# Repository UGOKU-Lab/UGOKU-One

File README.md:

UGOKU One のハードウェア（KiCad）リポジトリです。

[UGOKU One WEBサイト](https://ugoku-lab.github.io/ugokuone.html)

UGOKU One はモータやセンサを使ったロボットなどのDIY製作物を少しでも手軽に操作することを目的に開発しているオープンソースハードウェアの汎用基板です。
    
- 単四電池ボックス搭載で単四電池4本でDCモーターやRCサーボをの駆動が可能
- Arduinoで開発可能なESP32マイコン搭載(無線通信対応)
- DCモータドライバ（TB67H450FNG）を2個搭載
- 豊富な汎用IOポートでいろんな拡張が可能
- 圧着工具を使用せずにモーターやセンサーの配線が可能

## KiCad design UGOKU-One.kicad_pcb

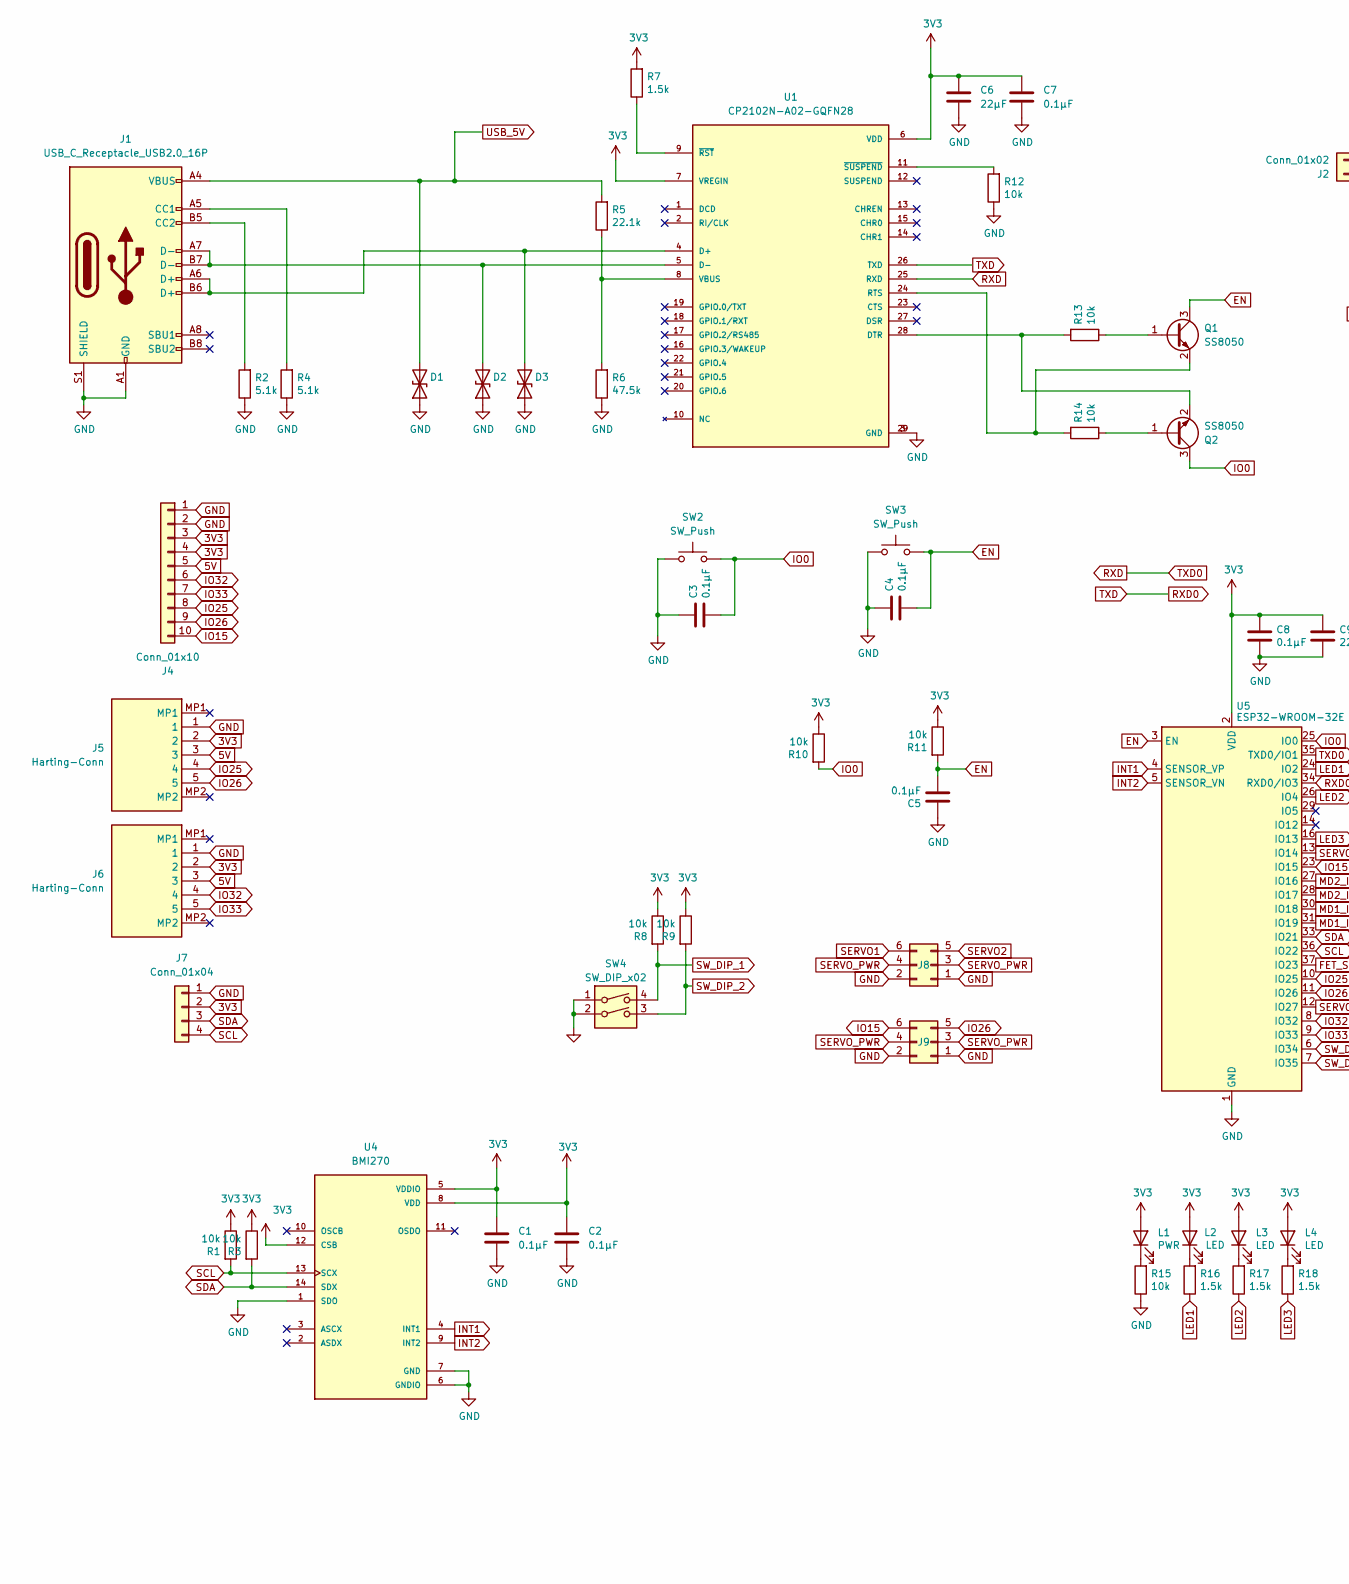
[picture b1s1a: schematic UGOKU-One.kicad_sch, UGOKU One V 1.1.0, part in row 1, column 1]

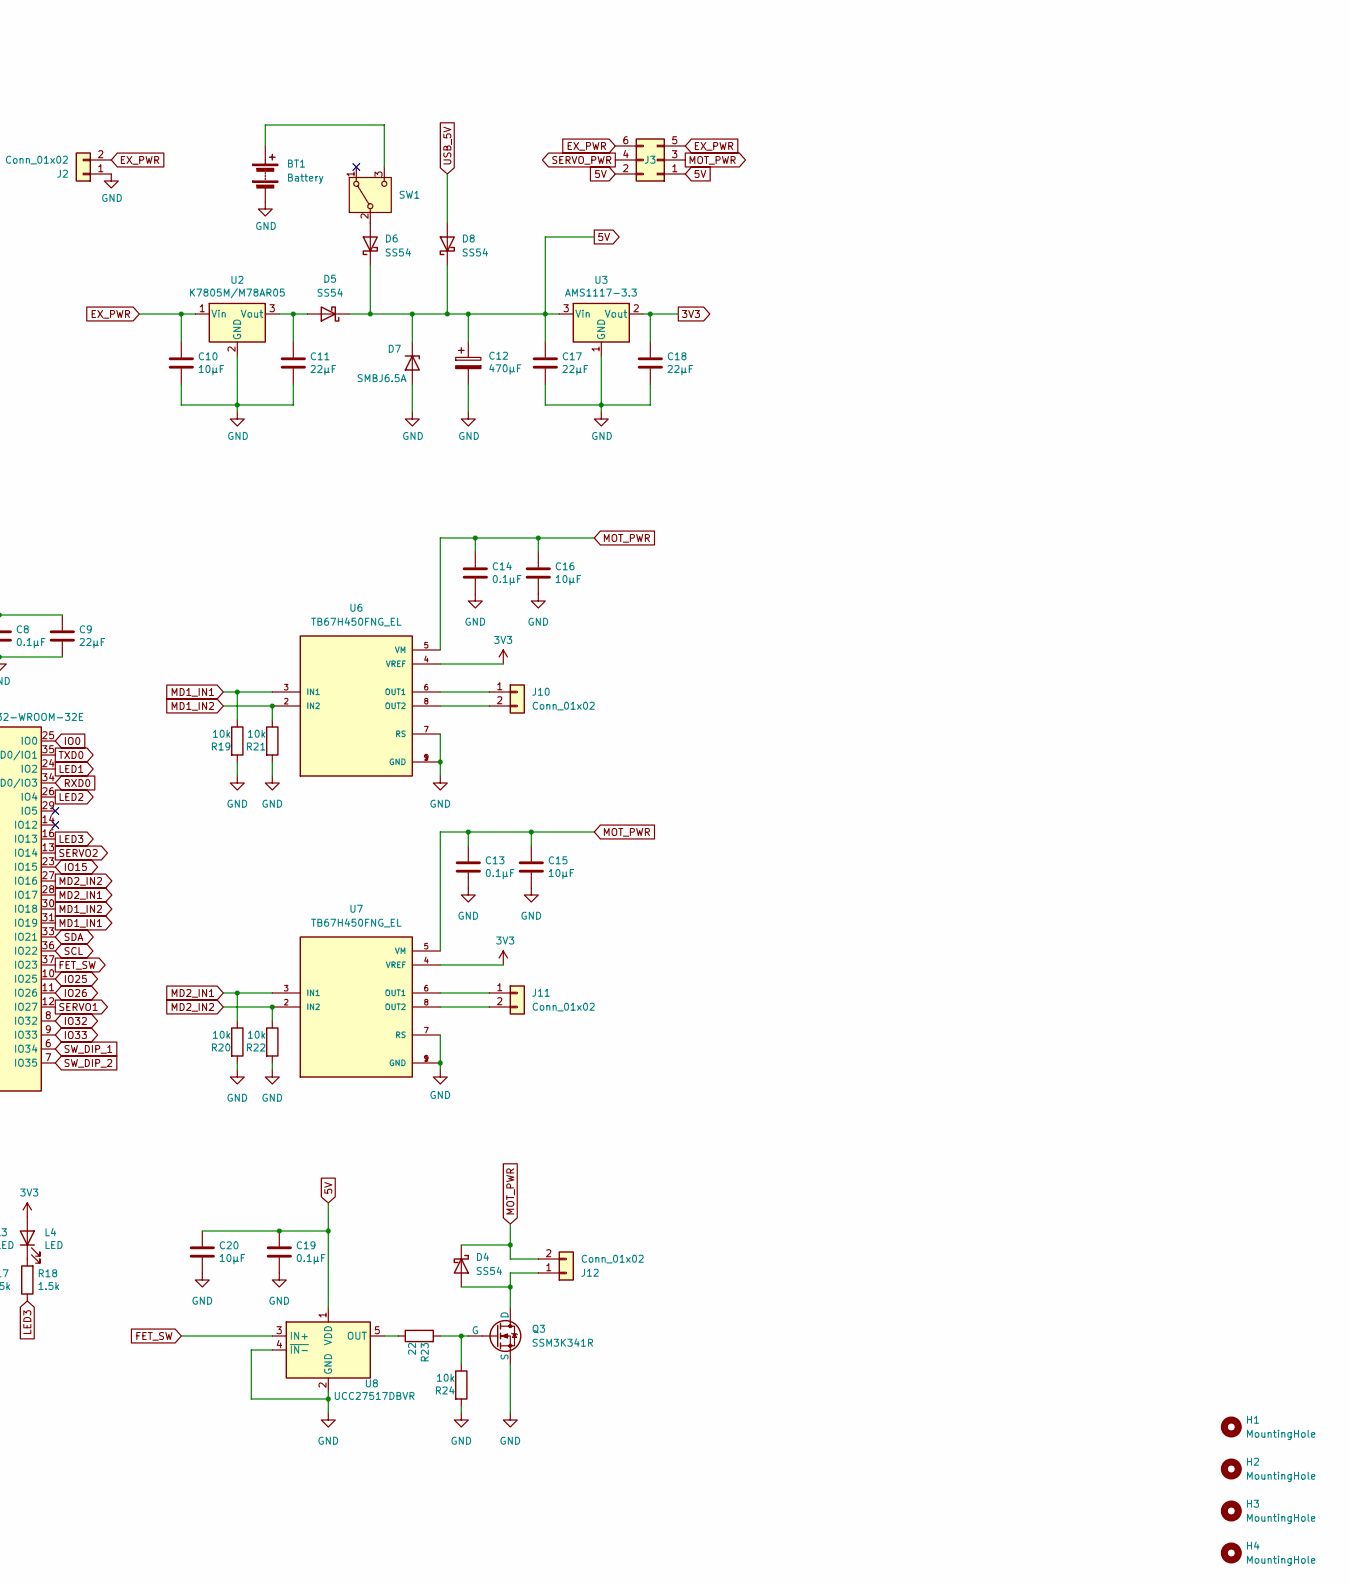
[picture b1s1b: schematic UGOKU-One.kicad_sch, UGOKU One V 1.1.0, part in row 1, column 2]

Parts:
BT1: Battery; BAT_2481
C1, C2, C3, C4, C5, C7, C8, C13, C14, C19: 0.1μF; C_0402_1005Metric
C6, C9, C11, C17, C18: 22μF; C_0805_2012Metric
C10, C15, C16, C20: 10μF; C_0805_2012Metric
C12: 470μF; CP_Elec_6.3x7.7
D1, D2, D3: LESD5D5.0CT1G; D_SOD-523
D4, D5, D6, D8: SS54; D_SMA
D7: SMBJ6.5A; D_SMB
H1, H2, H3, H4: MountingHole; MountingHole_3.2mm_M3
J1: USB_C_Receptacle_USB2.0_16P; USB_C_Receptacle_GCT_USB4105-xx-A_16P_TopMnt_Horizontal
J2, J10, J11, J12: Conn_01x02; PTS_1.5_2
J3, J8, J9: Conn_02x03_Odd_Even; PinHeader_2x03_P2.54mm_Vertical_SMD
J4: Conn_01x10; PinSocket_1x10_P2.54mm_Vertical
J5, J6: Harting-Conn; 14110513001000; Manufacturer_Part_Number 14110513001000; Mouser Part Number 617-14110513001000
J7: Conn_01x04; JST_XH_B4B-XH-A_1x04_P2.50mm_Vertical
L1: PWR; LED_0805_2012Metric_Pad1.15x1.40mm_HandSolder
L2, L3, L4: LED; LED_0805_2012Metric_Pad1.15x1.40mm_HandSolder
Q1, Q2: SS8050; SOT-23
Q3: SSM3K341R; SOT-23F
R1, R3, R8, R9, R10, R11, R12, R13, R14, R15, R19, R20, R21, R22, R24: 10k; R_0402_1005Metric
R2, R4: 5.1k; R_0402_1005Metric
R5: 22.1k; R_0402_1005Metric
R6: 47.5k; R_0402_1005Metric
R7, R16, R17, R18: 1.5k; R_0603_1608Metric
R23: 22; R_0603_1608Metric
SW1: SW_SPDT; SW_SS-12M11G5
SW2, SW3: SW_Push; SW_Push_1P1T_NO_Vertical_Wuerth_434133025816
SW4: SW_DIP_x02; SW_DIP_SPSTx02_Slide_Omron_A6S-210x_W8.9mm_P2.54mm
U1: CP2102N-A02-GQFN28; IC_CP2102N-A02-GQFN28R; PARTREV 1.5
U2: K7805M/M78AR05; M78AR
U3: AMS1117-3.3; SOT-223-3_TabPin2
U4: BMI270; XDCR_BMI270
U5: ESP32-WROOM-32E
U6, U7: TB67H450FNG_EL; HSOP-8-1EP_3.9x4.9mm_P1.27mm_EP2.3x2.3mm; PARTREV 3.0
U8: UCC27517DBVR; SOT-23-5

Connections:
3V3: C1.1, C2.1, C6.1, C7.1, C8.1, C9.1, C18.1, J4.3, J4.4, J5.2, J6.2, J7.2, L1.2 (A), L2.2 (A), L3.2 (A), L4.2 (A), R1.1, R3.1, R7.2, R8.1, R9.1, R10.1, R11.1, U1.6 (VDD), U1.7 (VREGIN), U3.2 (Vout), U4.5 (VDDIO), U4.8 (VDD), U4.12 (CSB), U5.2 (VDD), U6.4 (VREF), U7.4 (VREF)
5V: C12.1, C17.1, C19.1, C20.1, D5.1 (K), D6.1 (K), D7.1 (K), D8.1 (K), J3.1, J3.2, J4.5, J5.3, J6.3, U3.3 (Vin), U8.1 (VDD)
EN: C4.2, C5.2, Q1.3 (C), R11.2, SW3.2, U5.3 (EN)
EX_PWR: C10.1, J2.2, J3.5, J3.6, U2.1 (Vin)
FET_SW: U5.37 (IO23), U8.3 (IN+)
GND: BT1.2 (-), C1.2, C2.2, C3.1, C4.1, C5.1, C6.2, C7.2, C8.2, C9.2, C10.2, C11.2, C12.2, C13.2, C14.2, C15.2, C16.2, C17.2, C18.2, C19.2, C20.2, D1.1 (A1), D2.1 (A1), D3.1 (A1), D7.2 (A), J1.A1 (GND), J1.A12 (GND), J1.B1 (GND), J1.B12 (GND), J1.S1 (SHIELD), J2.1, J4.1, J4.2, J5.1, J6.1, J7.1, J8.1, J8.2, J9.1, J9.2, Q3.2 (S), R2.1, R4.1, R6.1, R12.1, R15.1, R19.2, R20.2, R21.2, R22.2, R24.2, SW2.1, SW3.1, SW4.1, SW4.2, U1.3 (GND), U1.29 (GND), U2.2 (GND), U3.1 (GND), U4.1 (SDO), U4.6 (GNDIO), U4.7 (GND), U5.1 (GND), U5.15 (GND), U5.38 (GND), U5.39 (GND), U6.1 (GND), U6.7 (RS), U6.9 (GND), U7.1 (GND), U7.7 (RS), U7.9 (GND), U8.2 (GND), U8.4 (~IN-)
INT1: U4.4 (INT1), U5.4 (SENSOR_VP)
INT2: U4.9 (INT2), U5.5 (SENSOR_VN)
IO0: C3.2, Q2.3 (C), R10.2, SW2.2, U5.25 (IO0)
IO15: J4.10, J9.6, U5.23 (IO15)
IO25: J4.8, J5.4, U5.10 (IO25)
IO26: J4.9, J5.5, J9.5, U5.11 (IO26)
IO32: J4.6, J6.4, U5.8 (IO32)
IO33: J4.7, J6.5, U5.9 (IO33)
LED1: R16.1, U5.24 (IO2)
LED2: R17.1, U5.26 (IO4)
LED3: R18.1, U5.16 (IO13)
MD1_IN1: R19.1, U5.31 (IO19), U6.3 (IN1)
MD1_IN2: R21.1, U5.30 (IO18), U6.2 (IN2)
MD2_IN1: R20.1, U5.28 (IO17), U7.3 (IN1)
MD2_IN2: R22.1, U5.27 (IO16), U7.2 (IN2)
MOT_PWR: C13.1, C14.1, C15.1, C16.1, D4.1 (K), J3.3, J12.2, U6.5 (VM), U7.5 (VM)
unnamed: BT1.1 (+), SW1.3 (C)
unnamed: D2.2 (A2), J1.A7 (D-), J1.B7 (D-), U1.5 (D-)
unnamed: D3.2 (A2), J1.A6 (D+), J1.B6 (D+), U1.4 (D+)
unnamed: D4.2 (A), J12.1, Q3.3 (D)
unnamed: C11.1, D5.2 (A), U2.3 (Vout)
unnamed: D6.2 (A), SW1.2 (B)
unnamed: J1.A5 (CC1), R4.2
unnamed: J1.B5 (CC2), R2.2
unnamed: J10.1, U6.6 (OUT1)
unnamed: J10.2, U6.8 (OUT2)
unnamed: J11.1, U7.6 (OUT1)
unnamed: J11.2, U7.8 (OUT2)
unnamed: L1.1 (K), R15.2
unnamed: L2.1 (K), R16.2
unnamed: L3.1 (K), R17.2
unnamed: L4.1 (K), R18.2
unnamed: Q1.1 (B), R13.1
unnamed: Q1.2 (E), R14.2, U1.24 (RTS)
unnamed: Q2.1 (B), R14.1
unnamed: Q2.2 (E), R13.2, U1.28 (DTR)
unnamed: Q3.1 (G), R23.2, R24.1
unnamed: R5.1, R6.2, U1.8 (VBUS)
unnamed: R7.1, U1.9 (~RST)
unnamed: R12.2, U1.11 (~SUSPEND)
unnamed: R23.1, U8.5 (OUT)
RXD: U1.25 (RXD), U5.35 (TXD0/IO1)
RXD0: U1.26 (TXD), U5.34 (RXD0/IO3)
SCL: J7.4, R1.2, U4.13 (SCX), U5.36 (IO22)
SDA: J7.3, R3.2, U4.14 (SDX), U5.33 (IO21)
SERVO1: J8.6, U5.12 (IO27)
SERVO2: J8.5, U5.13 (IO14)
SERVO_PWR: J3.4, J8.3, J8.4, J9.3, J9.4
SW_DIP_1: R8.2, SW4.4, U5.6 (IO34)
SW_DIP_2: R9.2, SW4.3, U5.7 (IO35)
USB_5V: D1.2 (A2), D8.2 (A), J1.A4 (VBUS), J1.A9 (VBUS), J1.B4 (VBUS), J1.B9 (VBUS), R5.2

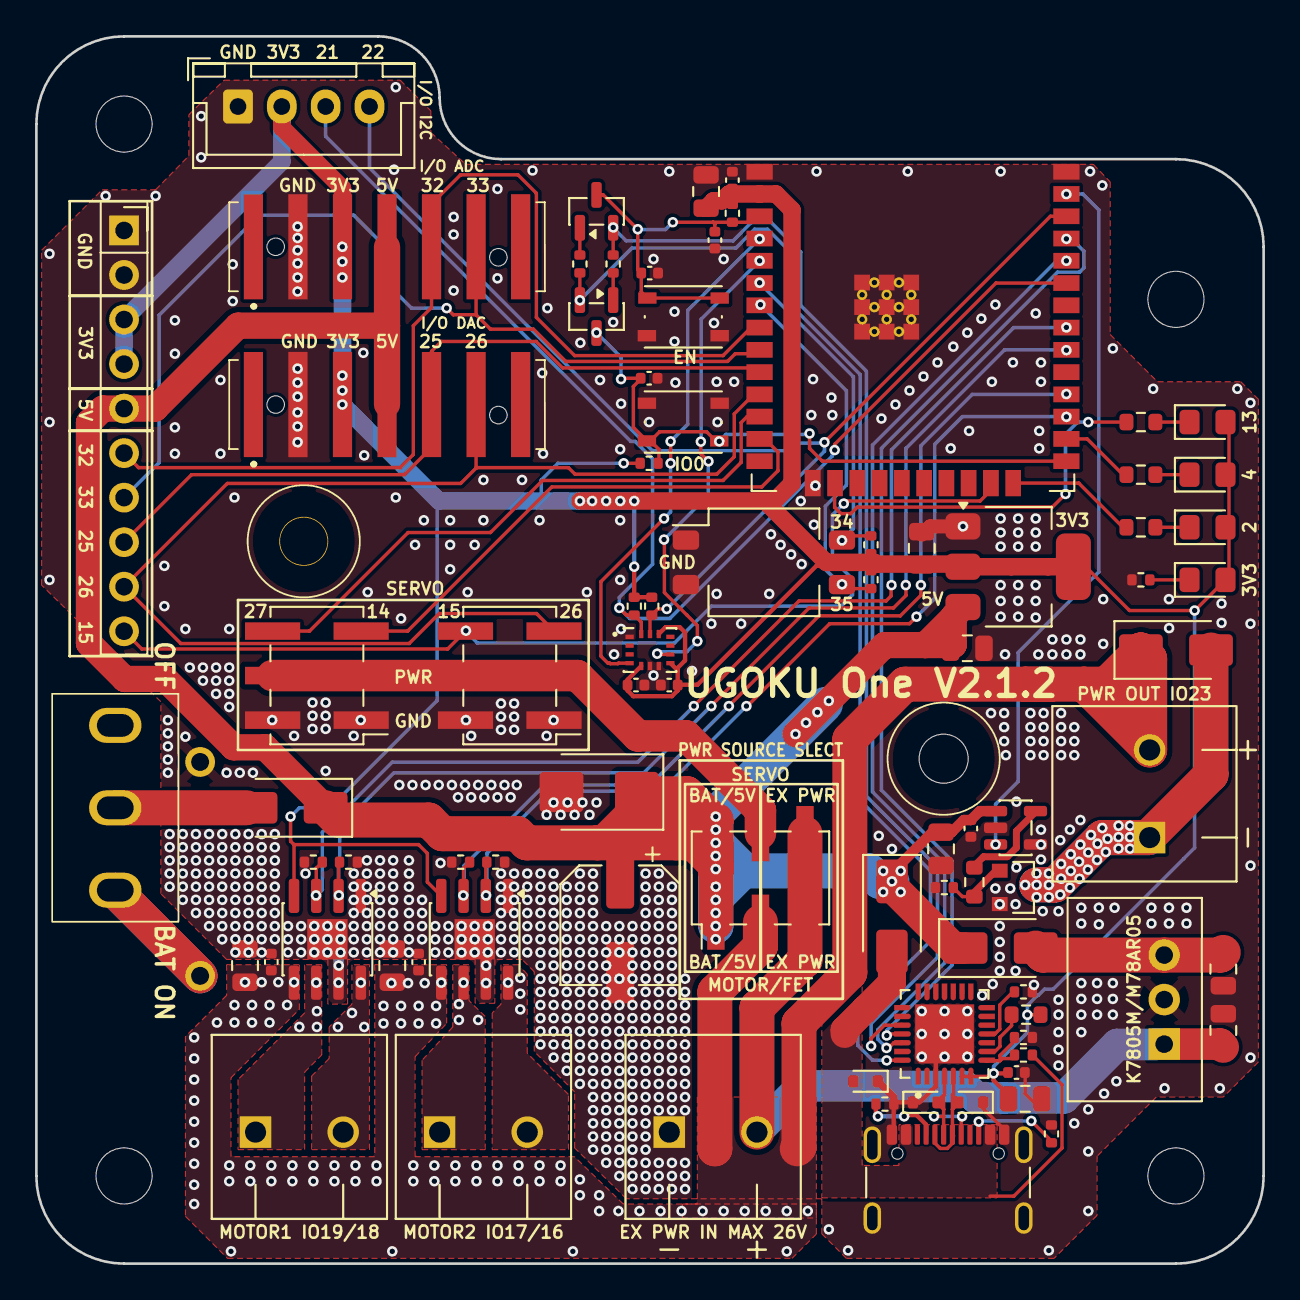
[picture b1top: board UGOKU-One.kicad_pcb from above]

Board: 2 copper layers, 70.0 x 70.0 mm, 88 parts (1 on the bottom side), 57 nets.

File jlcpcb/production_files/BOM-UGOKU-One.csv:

Comment,Designator,Footprint,LCSC,Quantity
0.1μF,"C1,C13,C14,C19,C2,C3,C4,C5,C7,C8",C_0402_1005Metric,C307331,10
1.5k,"R16,R17,R18,R7",R_0603_1608Metric,C22843,4
10k,"R1,R10,R11,R12,R13,R14,R15,R19,R20,R21,R22,R24,R3,R8,R9",R_0402_1005Metric,C25744,15
10μF,"C10,C15,C16,C20",C_0805_2012Metric,C440198,4
22,R23,R_0603_1608Metric,C23345,1
22.1k,R5,R_0402_1005Metric,C25768,1
22μF,"C11,C17,C18,C6,C9",C_0805_2012Metric,C45783,5
47.5k,R6,R_0402_1005Metric,C25792,1
470μF,C12,CP_Elec_6.3x7.7,C709470,1
5.1k,"R2,R4",R_0402_1005Metric,C25905,2
AMS1117-3.3,U3,SOT-223-3_TabPin2,C6186,1
BMI270,U4,XDCR_BMI270,C2836813,1
Battery,BT1,BAT_2481,C7174242,1
CP2102N-A02-GQFN28,U1,IC_CP2102N-A02-GQFN28R,C964632,1
Conn_01x02,"J10,J11,J12,J2",PTS_1.5_2,C3032345,4
Conn_01x10,J4,PinSocket_1x10_P2.54mm_Vertical,C2897373,1
Conn_02x03_Odd_Even,"J3,J8,J9",PinHeader_2x03_P2.54mm_Vertical_SMD,C3294461,3
ESP32-WROOM-32E,U5,ESP32-WROOM-32E,C701342,1
Harting-Conn,"J5,J6",14110513001000,C5475480,2
K7805M/M78AR05,U2,M78AR,C2992391,1
LED,"L2,L3,L4",LED_0805_2012Metric_Pad1.15x1.40mm_HandSolder,C84256,3
LESD5D5.0CT1G,"D1,D2,D3",D_SOD-523,C383211,3
PWR,L1,LED_0805_2012Metric_Pad1.15x1.40mm_HandSolder,C2297,1
SMBJ6.5A,D7,D_SMB,C41376096,1
SS54,"D4,D5,D6,D8",D_SMA,C22452,4
SS8050,"Q1,Q2",SOT-23,C2150,2
SSM3K341R,Q3,SOT-23F,C2932178,1
SW_DIP_x02,SW4,SW_DIP_SPSTx02_Slide_Omron_A6S-210x_W8.9mm_P2.54mm,C6331180,1
SW_Push,"SW2,SW3",SW_Push_1P1T_NO_Vertical_Wuerth_434133025816,C115360,2
SW_SPDT,SW1,SW_SS-12M11G5,C2879839,1
TB67H450FNG_EL,"U6,U7",HSOP-8-1EP_3.9x4.9mm_P1.27mm_EP2.3x2.3mm,C545417,2
UCC27517DBVR,U8,SOT-23-5,C99395,1
USB_C_Receptacle_USB2.0_16P,J1,USB_C_Receptacle_GCT_USB4105-xx-A_16P_TopMnt_Horizontal,C2765186,1
Conn_01x04,J7,JST_XH_B4B-XH-A_1x04_P2.50mm_Vertical,,1

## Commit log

2024-07-21 Hand over data from previous UGOKU-One (Now UGOKU-Pro)
2024-07-21 commit iroiro
2024-10-13 make concept
2025-03-17 modify usb, power
2025-03-22 add PD
2025-03-28 V1 Rough Layout
2025-03-30 Add IMU, FET
2025-03-31 power layout draft
2025-03-31 Remove cached KiCad temporary files
2025-04-03 Power:near complete
2025-04-16 Almost done
2025-05-04 April-22 order spec
2025-05-04 update 3dmodel connector color
2025-05-04 update parts 3dmodel path
2025-05-04 update 3dmodel path
2025-05-10 update 3dmodels
2025-05-16 correct TXRX, regulator pin assign add batt thermal pad
2025-05-18 Create LICENSE
2025-05-18 align resistor
2025-06-11 add Motor Drive IN1/2 PIN PullDown, IO0 PIN PullUp
2025-06-11 Add Title to sch, Update sch pdf
2025-06-14 JLCPCBの要求に対応するため最小viaサイズを0.3/0.5に変更、JLCPCBの要求に対応するためvia-Padクリアランス確保のため地磁気センサBMM150を廃止、スイッチング出力用FETのピン配置を修正
2025-06-14 IMUの待機電力が微小のため、IMUの電源スイッチを廃止
2025-07-27 add jlcpcb project.db
2025-08-15 電池ボックスボルトをM2.6に変更 JLCPCB tool 部品表の部品座標、向きを修正
2025-08-15 CPLファイルの座標と向きを修正、電池ボックスねじ締結指示の画像を追加
2025-08-18 add part lib
2025-08-23 change PWR connector SPTAF
2025-08-23 JLCPCB economy に対応するためIMUをICM-42605に変更
2025-08-24 ピン配置とコネクタ配置を変更
2025-08-31 Update README for ESP32 microcontroller description
2025-10-04 add website
2025-10-26 5V電源でアクチュエータを駆動する際の安定性および安全性向上のためにのためにTVSダイオードと電解コンデンサを追加 PCB上に配置（未配線）
2025-11-22 TVSダイオードをSMBJ6.0に変更
2025-12-04 5VラインのコンデンサとTVSダイオードの配線を実施 IMUをBMI270に戻し
2025-12-05 配線、ビア、シルクスクリーンの修正
2025-12-05 ベタGNDとviaを修正
2025-12-05 ベタGNDを修正
2025-12-06 MD周りのベタ, viaを修正 BOM,CPLファイルを整備
2025-12-06 最新の修正を反映
2025-12-07 ビアの位置を修正
2025-12-07 製造用CPLファイルの電池ボックスの位置を修正
2025-12-07 コスト削減のため抵抗の種類を統一
2025-12-08 抵抗の種類削減
2025-12-12 アノテーションを更新
2025-12-12 IOピンのラベル名とアノテーション番号を修正
2025-12-18 FETの型番を回路図に記載
2025-12-25 FET熱対策としてFET周りのパターンとviaを修正
2026-02-10 FET出力をゲートドライバ駆動に変更、左上のIoConnectorをXAにも対応
